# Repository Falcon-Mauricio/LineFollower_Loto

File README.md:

# 🌸 LineFollower Loto

**Loto** es un robot seguidor de línea diseñado para competir en la disciplina de **<a href="https://lnr-argentina.com.ar/reglamentos/Reglamento%20Carrera.pdf" target="_blank">Carrera</a>** (fondo negro con línea blanca) organizada por la **<a href="https://lnr-argentina.com.ar/" target="_blank">LNR</a>**. Su diseño está inspirado en los pétalos de una flor loto.

<div align="center">
  
</div>

<div align="center" style="display: flex; justify-content: center; gap: 10px; margin-top: 10px;">

</div>

---

## 🚀 Características principales

| Especificación | Detalle |
|----------------|---------|
| **Dimensiones** | 138 mm (ancho) x 136 mm (largo) |
| **Chasis** | PCB estructural + soporte de motores impreso en PLA |
| **Batería** | LiPo 3S 350 mAh |
| **Microcontrolador** | ESP32 |
| **Sensores** | 8 sensores QRE (QRE1113GR) |
| **Motores** | ProFast 12V 3600 RPM |
| **Driver de motores** | TA6586 |

---

## ⚡ Entradas / Salidas (I/O)

<table>
<tr>

<td>

### Entradas (sensores y botones)

| Pin ESP32 | Descripción |
|-----------|-------------|
| GPIO13 | QRE sensor 1 |
| GPIO27 | QRE sensor 2 |
| GPIO26 | QRE sensor 3 |
| GPIO25 | QRE sensor 4 |
| GPIO33 | QRE sensor 5 |
| GPIO32 | QRE sensor 6 |
| GPIO35 | QRE sensor 7 |
| GPIO34 | QRE sensor 8 |
| GPIO17 | Pulsador 1 |
| GPIO16 | Pulsador 2 |

</td>

<td>

### Salidas (motores y otros)

| Pin ESP32 | Descripción |
|-----------|-------------|
| GPIO19 | PWM A Motor 1 |
| GPIO21 | PWM B Motor 1 |
| GPIO22 | PWM A Motor 2 |
| GPIO23 | PWM B Motor 2 |
| GPIO04 | LED 1 |
| GPIO05 | LED 2 |
| GPIO18 | BUZZER |

</td>

</tr>
</table>

---

## 🛠 Tecnologías utilizadas

- **FreeCAD** → Diseño mecánico del soporte de motores y elementos impresos
- **KiCad** → Diseño del PCB
- **PlatformIO VisualStudioCODE** → Firmware para el ESP32

---

## 📂 Archivos

- `1_hardware_pcb/` → Archivos de KiCad (PCB + esquemas)  
- `2_hardware_3d/` → Archivos FreeCAD / STL de las piezas impresas
- `3_firmware/` → Código fuente para el ESP32
- `4_assets/` → Fotos y videos del robot  
- `docs/` → Diagramas, esquemas y documentación

---

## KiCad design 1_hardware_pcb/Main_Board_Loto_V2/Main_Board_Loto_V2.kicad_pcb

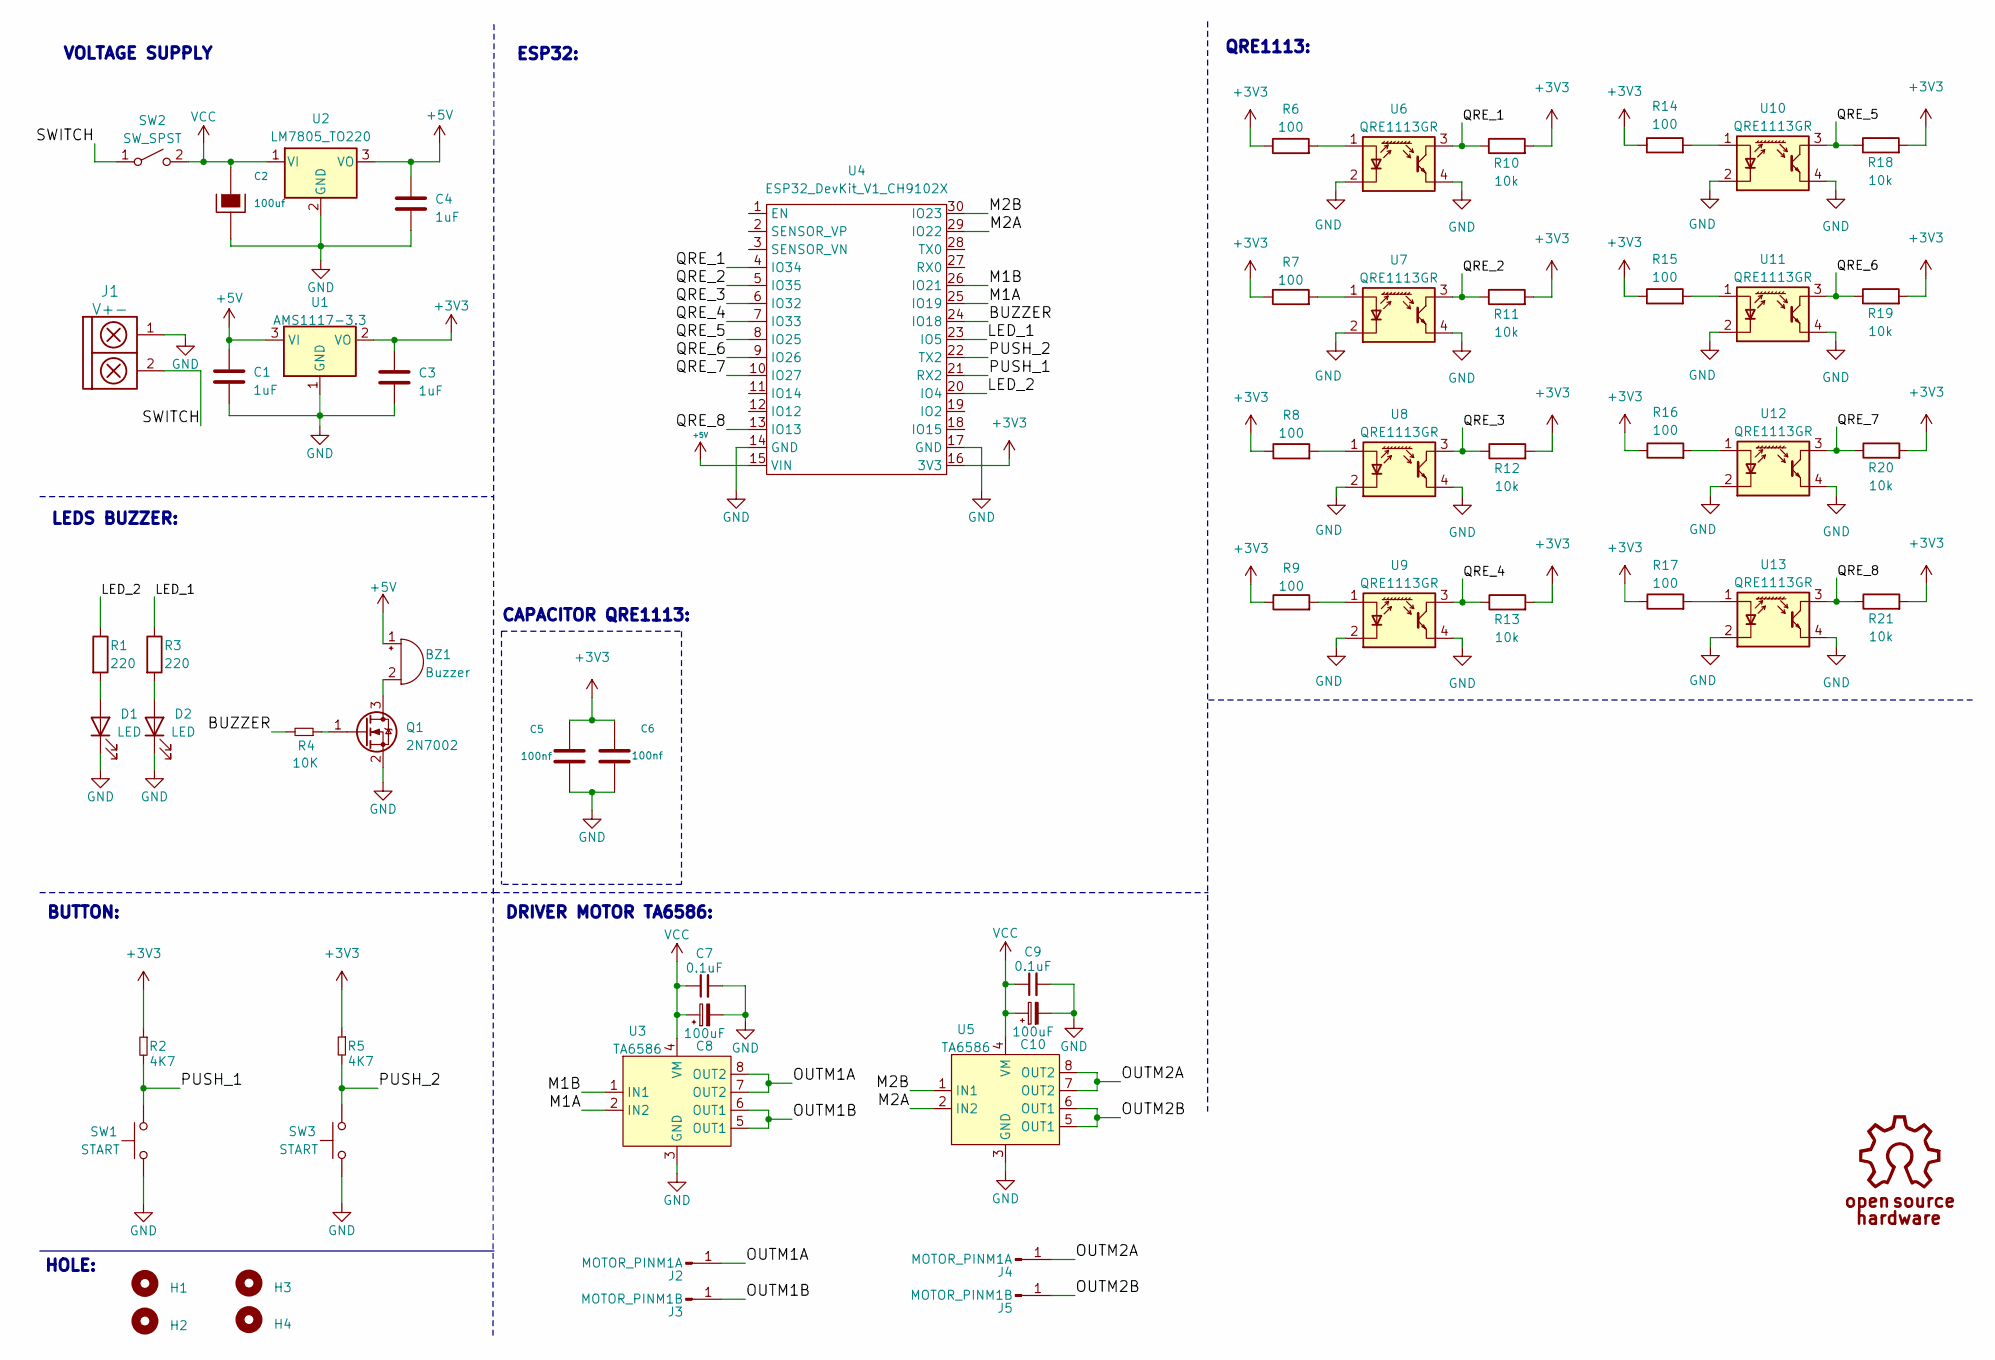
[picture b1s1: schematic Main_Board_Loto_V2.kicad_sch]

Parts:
BZ1: Buzzer; Buzzer_12mm
C1, C3, C4: 1uF; C_0805_2012Metric_Pad1.18x1.45mm_HandSolder
C2: 100uf; C_Radial_D10.0mm_H12.5mm_P5.00mm
C5, C6: 100nf; C_0805_2012Metric_Pad1.18x1.45mm_HandSolder
C7, C9: 0.1uF; C_0805
C8, C10: 100uF; CP_Radial_D5.0mm_P2.50mm
D1, D2: LED; led_5mm_clear
H1, H2, H3, H4: Mounting_Hole; hole_3mm
J1: V+-; BORNERA2_AZUL
J2, J4: MOTOR_PINM1A; Banana_Jack_1Pin
J3, J5: MOTOR_PINM1B; Banana_Jack_1Pin
Q1: 2N7002; SOT-23
R1, R3: 220; R_1206
R2, R5: 4K7; R_1206
R4: 10K; R_1206
R6, R7, R8, R9, R14, R15, R16, R17: 100; R_1206
R10, R11, R12, R13, R18, R19, R20, R21: 10k; R_1206
SW1, SW3: START; SW_PUSH_6mm_H5mm
SW2: SW_SPST; SW_SPDT_TH_Vertical
U1: AMS1117-3.3; SOT-223-3_TabPin2
U2: LM7805_TO220; TO-220-3_Vertical
U3, U5: TA6586; DIP-8_W7.62mm
U4: ESP32_DevKit_V1_CH9102X
U6, U7, U8, U9, U10, U11, U12, U13: QRE1113GR; OnSemi_CASE100CY

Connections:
+3V3: C3.1, C5.1, C6.1, R2.1, R5.1, R6.1, R7.1, R8.1, R9.1, R10.2, R11.2, R12.2, R13.2, R14.1, R15.1, R16.1, R17.1, R18.2, R19.2, R20.2, R21.2, U1.2 (VO), U4.16 (3V3)
+5V: BZ1.1 (-), C1.1, C4.1, U1.3 (VI), U2.3 (VO), U4.15 (VIN)
/BUZZER: R4.2, U4.24 (IO18)
/LED_1: R3.1, U4.23 (IO5)
/LED_2: R1.1, U4.20 (IO4)
/M1A: U3.2 (IN2), U4.25 (IO19)
/M1B: U3.1 (IN1), U4.26 (IO21)
/M2A: U4.29 (IO22), U5.2 (IN2)
/M2B: U4.30 (IO23), U5.1 (IN1)
/OUTM1A: J2.1, U3.7 (OUT2), U3.8 (OUT2)
/OUTM1B: J3.1, U3.5 (OUT1), U3.6 (OUT1)
/OUTM2A: J4.1, U5.7 (OUT2), U5.8 (OUT2)
/OUTM2B: J5.1, U5.5 (OUT1), U5.6 (OUT1)
/PUSH_1: R2.2, SW1.2, U4.21 (RX2)
/PUSH_2: R5.2, SW3.2, U4.22 (TX2)
/QRE_1: R10.1, U4.4 (IO34), U6.3
/QRE_2: R11.1, U4.5 (IO35), U7.3
/QRE_3: R12.1, U4.6 (IO32), U8.3
/QRE_4: R13.1, U4.7 (IO33), U9.3
/QRE_5: R18.1, U4.8 (IO25), U10.3
/QRE_6: R19.1, U4.9 (IO26), U11.3
/QRE_7: R20.1, U4.10 (IO27), U12.3
/QRE_8: R21.1, U4.13 (IO13), U13.3
/SWITCH: J1.2, SW2.1 (A)
GND: C1.2, C2.2, C3.2, C4.2, C5.2, C6.2, C7.2, C8.2, C9.2, C10.2, D1.1 (K), D2.1 (K), J1.1, Q1.2 (S), SW1.1, SW3.1, U1.1 (GND), U2.2 (GND), U3.3 (GND), U4.14 (GND), U4.17 (GND), U5.3 (GND), U6.2 (K), U6.4, U7.2 (K), U7.4, U8.2 (K), U8.4, U9.2 (K), U9.4, U10.2 (K), U10.4, U11.2 (K), U11.4, U12.2 (K), U12.4, U13.2 (K), U13.4
unnamed: BZ1.2 (+), Q1.3 (D)
unnamed: D1.2 (A), R1.2
unnamed: D2.2 (A), R3.2
unnamed: Q1.1 (G), R4.1
unnamed: R6.2, U6.1 (A)
unnamed: R7.2, U7.1 (A)
unnamed: R8.2, U8.1 (A)
unnamed: R9.2, U9.1 (A)
unnamed: R14.2, U10.1 (A)
unnamed: R15.2, U11.1 (A)
unnamed: R16.2, U12.1 (A)
unnamed: R17.2, U13.1 (A)
VCC: C2.1, C7.1, C8.1, C9.1, C10.1, SW2.2 (B), U2.1 (VI), U3.4 (VM), U5.4 (VM)

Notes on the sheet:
ESP32:
CAPACITOR QRE1113:
HOLE:
VOLTAGE SUPPLY
BUTTON:
LEDS BUZZER:
QRE1113:
DRIVER MOTOR TA6586:

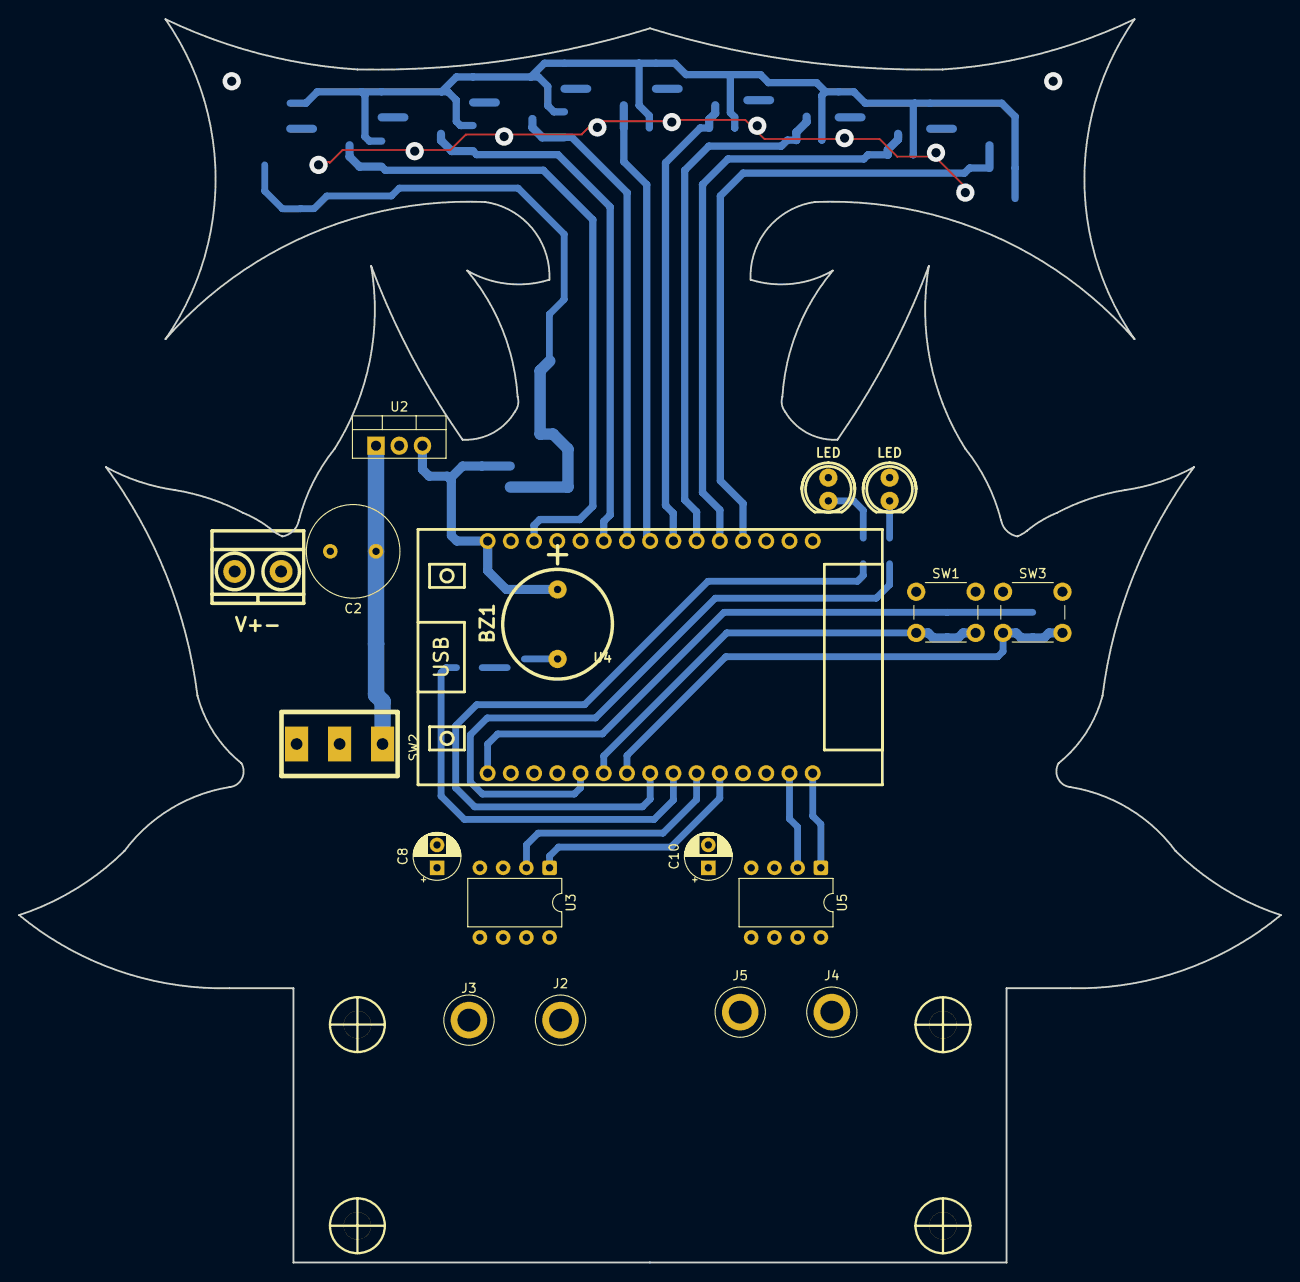
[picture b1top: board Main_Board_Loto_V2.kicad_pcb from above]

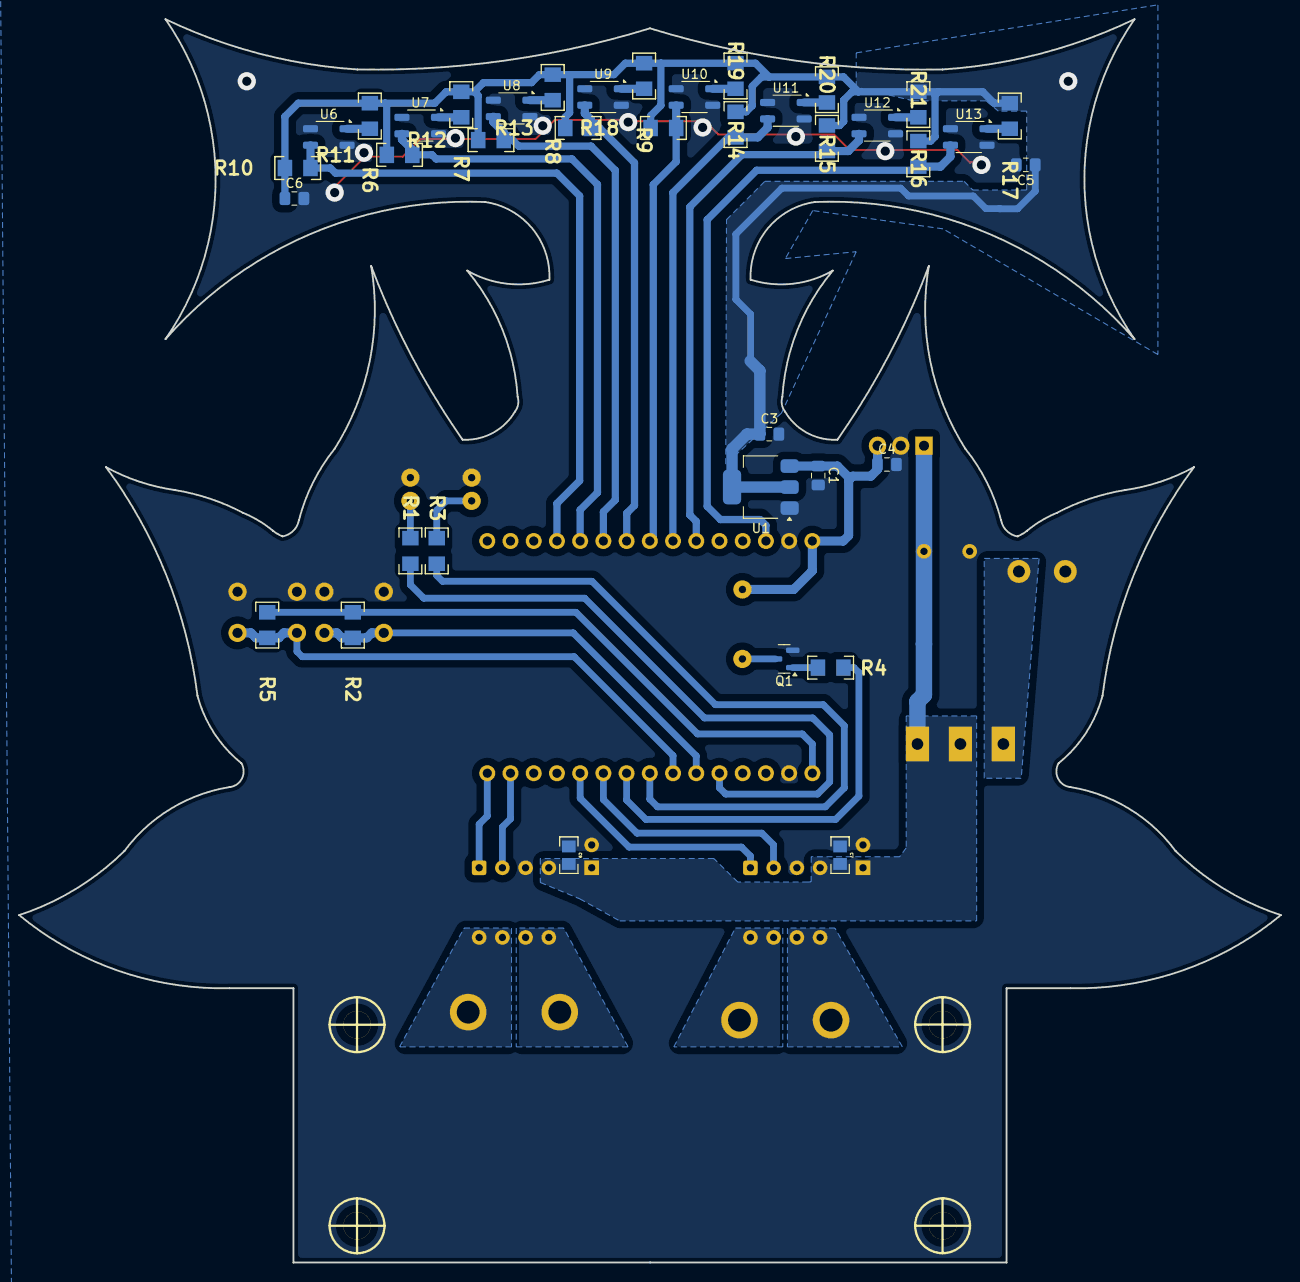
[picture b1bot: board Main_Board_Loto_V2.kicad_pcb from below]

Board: 2 copper layers, 138.0 x 136.0 mm, 60 parts (38 on the bottom side), 38 nets.

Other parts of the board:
H3#2, H4#2: Mounting_Hole; hole_3mm

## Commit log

2025-06-09 Creacion del proyecto kicad para el PCB
2025-06-09 SCH terminado
2025-06-11 Definida la ubicacion de los componentes y enrutadas las vias de los mismos
2025-06-15 Cntorno de PCB diseñad en FreeCAD y PCB terminad en Kicad
2025-06-15 Soporte para motor incluido en el PCB y generadas las imagenes de fabricacion
2025-06-17 Pistas de 0.75 pasaron a 0.8 por temas de CNC
2025-06-18 Generacion de PDF y SVG para fabricacion en CNC
2025-07-22 Diseñado el Soporte para motor ProFast
2025-07-23 Diseñada la llante para rueda de 30x30
2025-07-24 Diseñado el molde para la cubierta de 30x30
2025-08-15 Cambie la placa generando la V2 y ordene el repo
